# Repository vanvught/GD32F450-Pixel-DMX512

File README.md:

#GD32F450 Pixel DMX512

Features: 

- 16x 4 Universes pixel output
- 2x  1 Universe DMX output
- EEPROM for storing the configuration
- 1x I2C (display)
- 1x SPI
- 2x UART (WiFi , Bluetooth)

Firmware: [https://github.com/vanvught/GD32F450VI-DMX512-PIXEL](https://github.com/vanvught/GD32F450VI-DMX512-PIXEL)

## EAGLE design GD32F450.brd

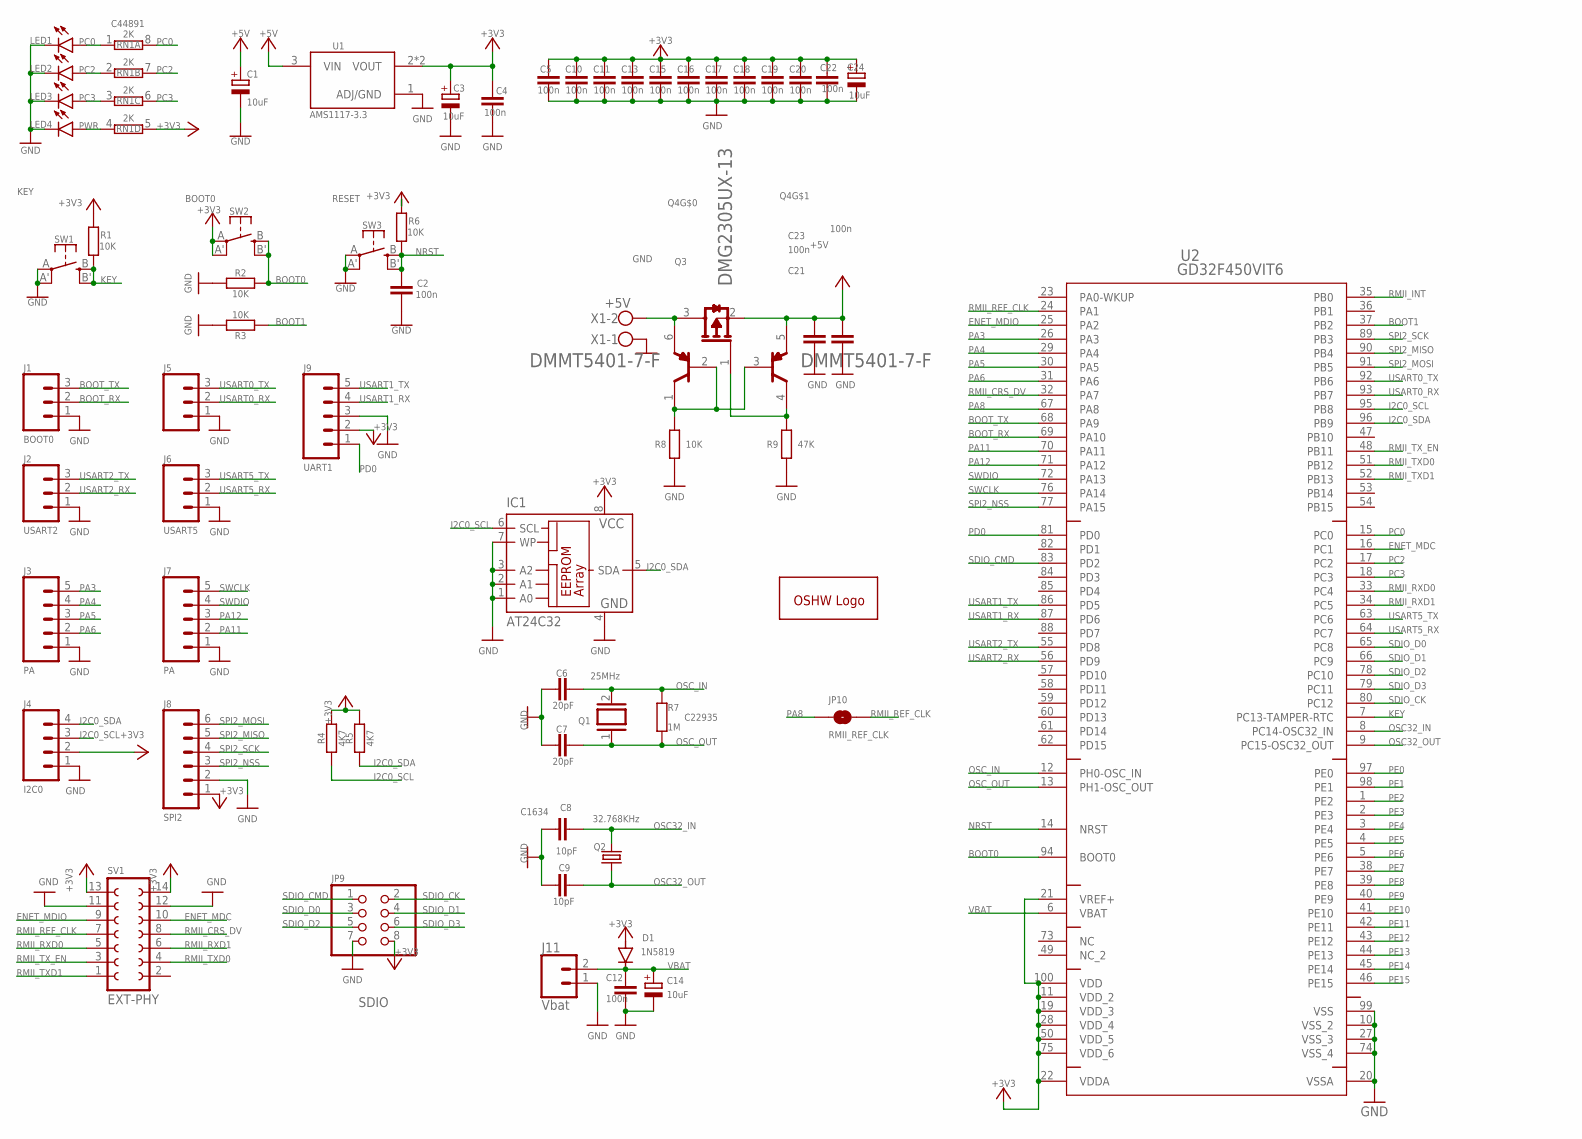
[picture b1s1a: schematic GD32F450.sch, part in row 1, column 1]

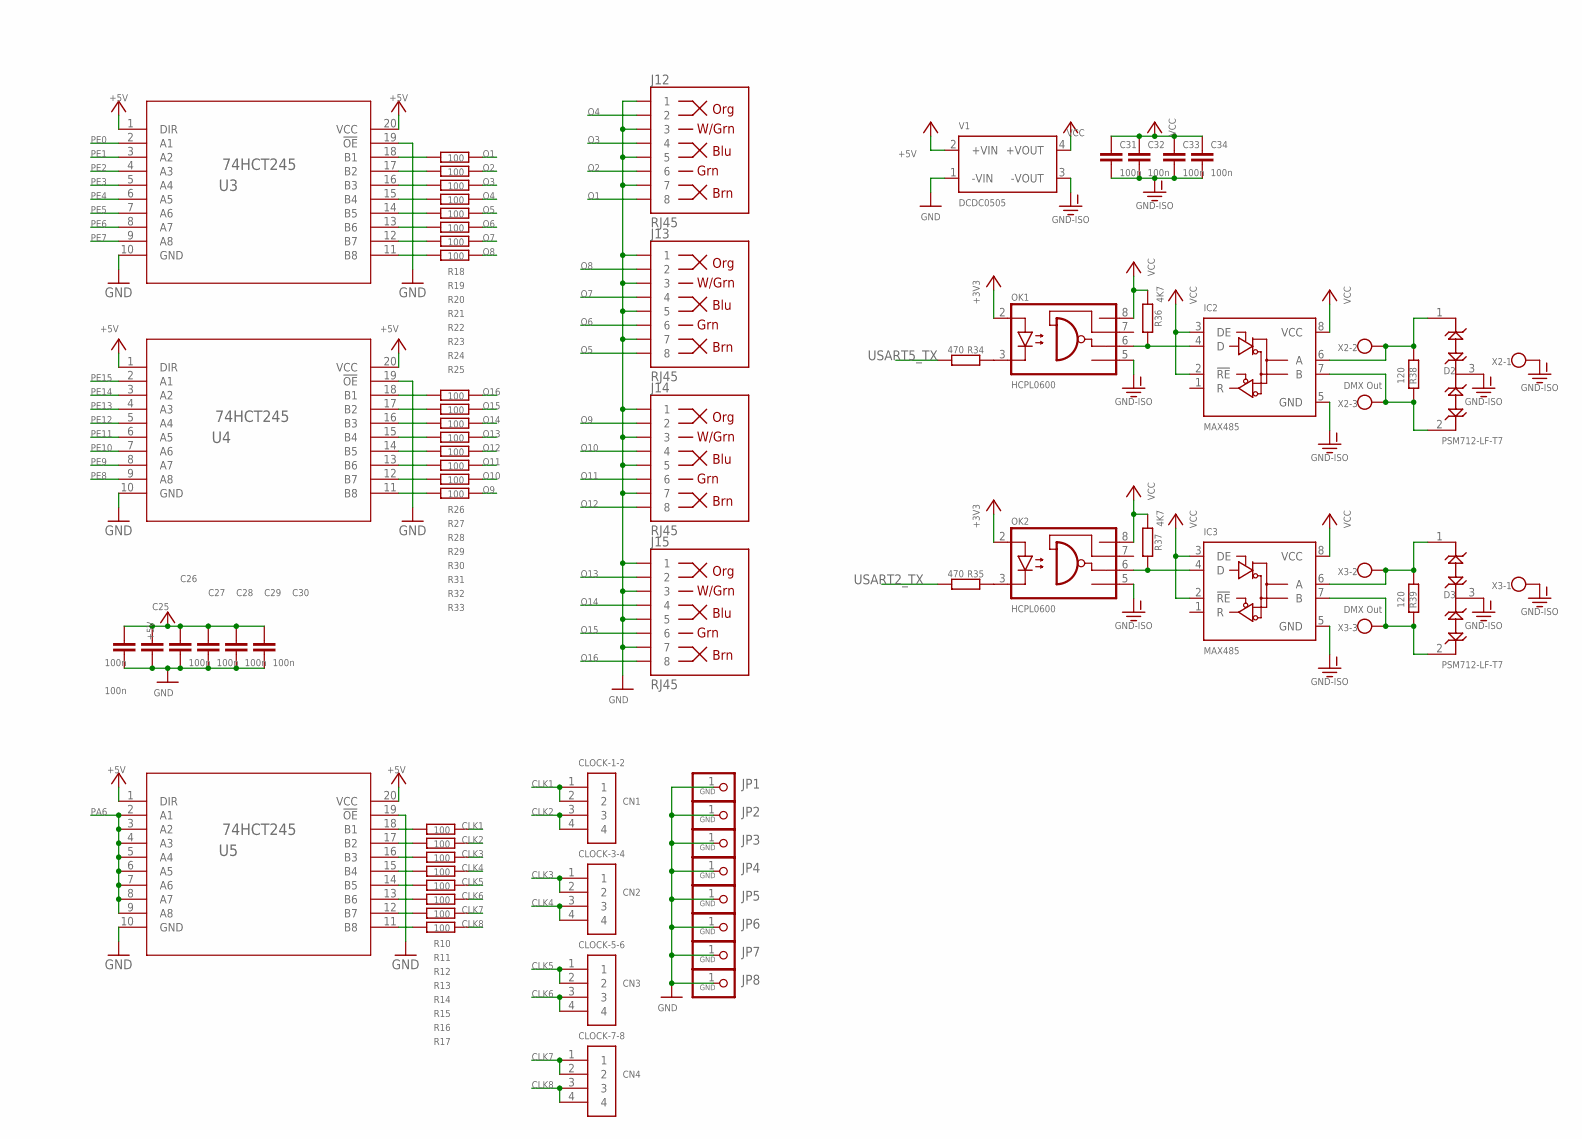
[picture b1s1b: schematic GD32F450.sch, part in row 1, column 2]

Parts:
C1, C3, C14, C24: 10uF; A/3216-18R; JLCPCB C7171
C2, C4, C5, C10, C11, C12, C13, C15, C16, C17, C18, C19, C20, C22, C25, C26, C27, C28, C29, C30, C31, C32, C33, C34: 100n; C0603; JLCPCB C14663
C6, C7: 20pF; C0603; JLCPCB C1648
C8, C9: 10pF; C0603; JLCPCB C1634
C21, C23: 100n; C0603
CN1: CLOCK-1-2; 1X04-CLEANBIG
CN2: CLOCK-3-4; 1X04-CLEANBIG
CN3: CLOCK-5-6; 1X04-CLEANBIG
CN4: CLOCK-7-8; 1X04-CLEANBIG
D1: 1N5819; SOD323-R; JLCPCB C191023
D2, D3: PSM712-LF-T7; SOT23-3; JLCPCB C32677
GOLD_ORB_SM1: OSHWLOGOLOGO5MM; OSHW_5MM
IC1: AT24C32; SO-08M
IC2, IC3: MAX485; D_R-PDSO-G8; JLCPCB C23492
J1: BOOT0; 1X03
J2: USART2; 1X03
J3, J7: PA; 1X05
J4: I2C0; 1X04
J5: USART0; 1X03
J6: USART5; 1X03
J8: SPI2; 1X06
J9: UART1; 1X05
J11: Vbat; 1X02_NO_SILK
J12, J13, J14, J15: RJ45; RJ45-8
JP1, JP2, JP3, JP4, JP5, JP6, JP7, JP8: GND; 1X01-CLEANBIG
JP9: SDIO; 2X04
JP10: RMII_REF_CLK; SMT-JUMPER_2_NO_NO-SILK
LED1: PC0; CHIP-LED0603
LED2: PC2; CHIP-LED0603
LED3: PC3; CHIP-LED0603
LED4: PWR; CHIP-LED0603
OK1, OK2: HCPL0600; SOIC08; JLCPCB C393524
Q1: 25MHz; QS
Q2: 32.768KHz; TC26H
Q3: DMG2305UX; DIODES_INC._DMG2305UX-13_0
Q4: DMMT5401; DIODES_DMMT5401-7-F_0
R1, R2, R3, R6: 10K; R0603; JLCPCB C25804
R4, R5: 4K7; R0402; JLCPCB C23162
R7: 1M; R0603; JLCPCB C22935
R8: 10K; R0402
R9: 47K; R0402
R10, R11, R12, R13, R14, R15, R16, R17, R18, R19, R20, R21, R22, R23, R24, R25, R26, R27, R28, R29, R30, R31, R32, R33: 100; R0402
R34, R35: 470; R0402; JLCPCB C25117
R36, R37: 4K7; R0402; JLCPCB C275348
R38, R39: 120; R0402; JLCPCB C25079
RN1: 2K; 4X0402ARV341; JLCPCB C44891
SV1: EXT-PHY; FE07-2W
SW1: KEY; EVQ-Q2
SW2: BOOT0; EVQ-Q2; JLCPCB C221880
SW3: RESET; EVQ-Q2
U1: AMS1117-3.3; SOT229P700X180-4N
U2: GD32F450VIT6; LQFP100
U3, U4, U5: 74HCT245; PW20
V1: DCDC0505; TME
X1: +5V; W237-102
X2, X3: DMX Out; W237-103

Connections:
+3V3: C3.+, C4.1, C5.1, C10.1, C11.1, C13.1, C15.1, C16.1, C17.1, C18.1, C19.1, C20.1, C22.1, C24.+, D1.A, IC1.8 (VCC), J4.2, J8.1, J9.2, JP9.8, OK1.2 (A), OK2.2 (A), R1.2, R4.2, R5.2, R6.2, RN1.5 (2), SV1.13, SV1.14, SW2.A, SW2.A' (P1), U1.2 (VOUT), U1.4 (VOUT), U2.11 (VDD_2), U2.19 (VDD_3), U2.21 (VREF+), U2.22 (VDDA), U2.28 (VDD_4), U2.50 (VDD_5), U2.75 (VDD_6), U2.100 (VDD)
+5V: C1.+, C21.1, C23.1, C25.1, C26.1, C27.1, C28.1, C29.1, C30.1, Q3.2 (S), Q4.5 (E2), U1.3 (VIN), U3.1 (DIR), U3.20 (VCC), U4.1 (DIR), U4.20 (VCC), U5.1 (DIR), U5.20 (VCC), V1.2 (+VIN)
BOOT0: R2.2, SW2.B (S), SW2.B' (S1), U2.94 (BOOT0)
BOOT1: R3.1, U2.37 (PB2)
BOOT_RX: J1.2, U2.69 (PA10)
BOOT_TX: J1.3, U2.68 (PA9)
CLK1: CN1.1, CN1.2, R10.2
CLK2: CN1.3, CN1.4, R11.2
CLK3: CN2.1, CN2.2, R12.2
CLK4: CN2.3, CN2.4, R13.2
CLK5: CN3.1, CN3.2, R14.2
CLK6: CN3.3, CN3.4, R15.2
CLK7: CN4.1, CN4.2, R16.2
CLK8: CN4.3, CN4.4, R17.2
ENET_MDC: SV1.10, U2.16 (PC1)
ENET_MDIO: SV1.9, U2.25 (PA2)
GND: C1.-, C2.2, C3.-, C4.2, C5.2, C6.1, C7.1, C8.1, C9.1, C10.2, C11.2, C12.2, C13.2, C14.-, C15.2, C16.2, C17.2, C18.2, C19.2, C20.2, C21.2, C22.2, C23.2, C24.-, C25.2, C26.2, C27.2, C28.2, C29.2, C30.2, IC1.1 (A0), IC1.2 (A1), IC1.3 (A2), IC1.4 (GND), IC1.7 (WP), J1.1, J2.1, J3.1, J4.1, J5.1, J6.1, J7.1, J8.2, J9.3, J11.1, J12.1, J12.3, J12.5, J12.7, J13.1, J13.3, J13.5, J13.7, J14.1, J14.3, J14.5, J14.7, J15.1, J15.3, J15.5, J15.7, JP1.1, JP2.1, JP3.1, JP4.1, JP5.1, JP6.1, JP7.1, JP8.1, JP9.7, LED1.C, LED2.C, LED3.C, LED4.C, R2.1, R3.2, R8.1, R9.1, SV1.11, SV1.12, SW1.A, SW1.A' (P1), SW3.A, SW3.A' (P1), U1.1 (ADJ/GND), U2.10 (VSS_2), U2.20 (VSSA), U2.27 (VSS_3), U2.74 (VSS_4), U2.99 (VSS), U3.10 (GND), U3.19 (!OE), U4.10 (GND), U4.19 (!OE), U5.10 (GND), U5.19 (!OE), V1.1 (-VIN), X1.1
GND-ISO: C31.2, C32.2, C33.2, C34.2, D2.3, D3.3, IC2.5 (GND), IC3.5 (GND), OK1.5 (GND), OK2.5 (GND), V1.3 (-VOUT), X2.1, X3.1
I2C0_SCL: IC1.6 (SCL), J4.3, R4.1, U2.95 (PB8)
I2C0_SDA: IC1.5 (SDA), J4.4, R5.1, U2.96 (PB9)
KEY: R1.1, SW1.B (S), SW1.B' (S1), U2.7 (PC13-TAMPER-RTC)
unnamed: R18.1, U3.18 (B1)
unnamed: Q4.1 (C1), Q4.2 (B1), Q4.3 (B2), R8.2
unnamed: R19.1, U3.17 (B2)
unnamed: R20.1, U3.16 (B3)
unnamed: R21.1, U3.15 (B4)
unnamed: R22.1, U3.14 (B5)
unnamed: R23.1, U3.13 (B6)
unnamed: R24.1, U3.12 (B7)
unnamed: R25.1, U3.11 (B8)
unnamed: LED1.A, RN1.1
unnamed: LED2.A, RN1.2 (1)
unnamed: R26.1, U4.18 (B1)
unnamed: R27.1, U4.17 (B2)
unnamed: R28.1, U4.16 (B3)
unnamed: R29.1, U4.15 (B4)
unnamed: R30.1, U4.14 (B5)
unnamed: R31.1, U4.13 (B6)
unnamed: R32.1, U4.12 (B7)
unnamed: R33.1, U4.11 (B8)
unnamed: IC2.4 (D), OK1.6 (VO), R36.2
unnamed: OK1.3 (C), R34.2
unnamed: IC3.4 (D), OK2.6 (VO), R37.2
unnamed: OK2.3 (C), R35.2
unnamed: D2.1, IC2.6 (A), R38.1, X2.2
unnamed: LED3.A, RN1.3 (1)
unnamed: LED4.A, RN1.4 (1)
unnamed: D2.2, IC2.7 (B), R38.2, X2.3
unnamed: D3.2, IC3.7 (B), R39.2, X3.3
unnamed: D3.1, IC3.6 (A), R39.1, X3.2
unnamed: Q3.1 (G), Q4.4 (C2), R9.2
unnamed: Q3.3 (D), Q4.6 (E1), X1.2
unnamed: R10.1, U5.18 (B1)
unnamed: R11.1, U5.17 (B2)
unnamed: R12.1, U5.16 (B3)
unnamed: R13.1, U5.15 (B4)
unnamed: R14.1, U5.14 (B5)
unnamed: R15.1, U5.13 (B6)
unnamed: R16.1, U5.12 (B7)
unnamed: R17.1, U5.11 (B8)
NRST: C2.1, R6.1, SW3.B (S), SW3.B' (S1), U2.14 (NRST)
O1: J12.8, R18.2
O2: J12.6, R19.2
O3: J12.4, R20.2
O4: J12.2, R21.2
O5: J13.8, R22.2
O6: J13.6, R23.2
O7: J13.4, R24.2
O8: J13.2, R25.2
O9: J14.2, R33.2
O10: J14.4, R32.2
O11: J14.6, R31.2
O12: J14.8, R30.2
O13: J15.2, R29.2
O14: J15.4, R28.2
O15: J15.6, R27.2
O16: J15.8, R26.2
OSC32_IN: C8.2, Q2.2, U2.8 (PC14-OSC32_IN)
OSC32_OUT: C9.2, Q2.1, U2.9 (PC15-OSC32_OUT)
OSC_IN: C6.2, Q1.2, R7.2, U2.12 (PH0-OSC_IN)
OSC_OUT: C7.2, Q1.1, R7.1, U2.13 (PH1-OSC_OUT)
PA3: J3.5, U2.26 (PA3)
PA4: J3.4, U2.29 (PA4)
PA5: J3.3, U2.30 (PA5)
PA6: J3.2, U2.31 (PA6), U5.2 (A1), U5.3 (A2), U5.4 (A3), U5.5 (A4), U5.6 (A5), U5.7 (A6), U5.8 (A7), U5.9 (A8)
PA8: JP10.1, U2.67 (PA8)
PA11: J7.2, U2.70 (PA11)
PA12: J7.3, U2.71 (PA12)
PC0: RN1.8 (2), U2.15 (PC0)
PC2: RN1.7 (2), U2.17 (PC2)
PC3: RN1.6 (2), U2.18 (PC3)
PD0: J9.1, U2.81 (PD0)
PE0: U2.97 (PE0), U3.2 (A1)
PE1: U2.98 (PE1), U3.3 (A2)
PE2: U2.1 (PE2), U3.4 (A3)
PE3: U2.2 (PE3), U3.5 (A4)
PE4: U2.3 (PE4), U3.6 (A5)
PE5: U2.4 (PE5), U3.7 (A6)
PE6: U2.5 (PE6), U3.8 (A7)
PE7: U2.38 (PE7), U3.9 (A8)
PE8: U2.39 (PE8), U4.9 (A8)
PE9: U2.40 (PE9), U4.8 (A7)
PE10: U2.41 (PE10), U4.7 (A6)
PE11: U2.42 (PE11), U4.6 (A5)
PE12: U2.43 (PE12), U4.5 (A4)
PE13: U2.44 (PE13), U4.4 (A3)
PE14: U2.45 (PE14), U4.3 (A2)
PE15: U2.46 (PE15), U4.2 (A1)
RMII_CRS_DV: SV1.8, U2.32 (PA7)
RMII_INT: U2.35 (PB0)
RMII_REF_CLK: JP10.2, SV1.7, U2.24 (PA1)
RMII_RXD0: SV1.5, U2.33 (PC4)
RMII_RXD1: SV1.6, U2.34 (PC5)
RMII_TXD0: SV1.4, U2.51 (PB12)
RMII_TXD1: SV1.1, U2.52 (PB13)
RMII_TX_EN: SV1.3, U2.48 (PB11)
SDIO_CK: JP9.2, U2.80 (PC12)
SDIO_CMD: JP9.1, U2.83 (PD2)
SDIO_D0: JP9.3, U2.65 (PC8)
SDIO_D1: JP9.4, U2.66 (PC9)
SDIO_D2: JP9.5, U2.78 (PC10)
SDIO_D3: JP9.6, U2.79 (PC11)
SPI2_MISO: J8.5, U2.90 (PB4)
SPI2_MOSI: J8.6, U2.91 (PB5)
SPI2_NSS: J8.3, U2.77 (PA15)
SPI2_SCK: J8.4, U2.89 (PB3)
SWCLK: J7.5, U2.76 (PA14)
SWDIO: J7.4, U2.72 (PA13)
USART0_RX: J5.2, U2.93 (PB7)
USART0_TX: J5.3, U2.92 (PB6)
USART1_RX: J9.4, U2.87 (PD6)
USART1_TX: J9.5, U2.86 (PD5)
USART2_RX: J2.2, U2.56 (PD9)
USART2_TX: J2.3, R35.1, U2.55 (PD8)
USART5_RX: J6.2, U2.64 (PC7)
USART5_TX: J6.3, R34.1, U2.63 (PC6)
VBAT: C12.1, C14.+, D1.C, J11.2, U2.6 (VBAT)
VCC: C31.1, C32.1, C33.1, C34.1, IC2.2 (!RE), IC2.3 (DE), IC2.8 (VCC), IC3.2 (!RE), IC3.3 (DE), IC3.8 (VCC), OK1.8 (VCC), OK2.8 (VCC), R36.1, R37.1, V1.4 (+VOUT)

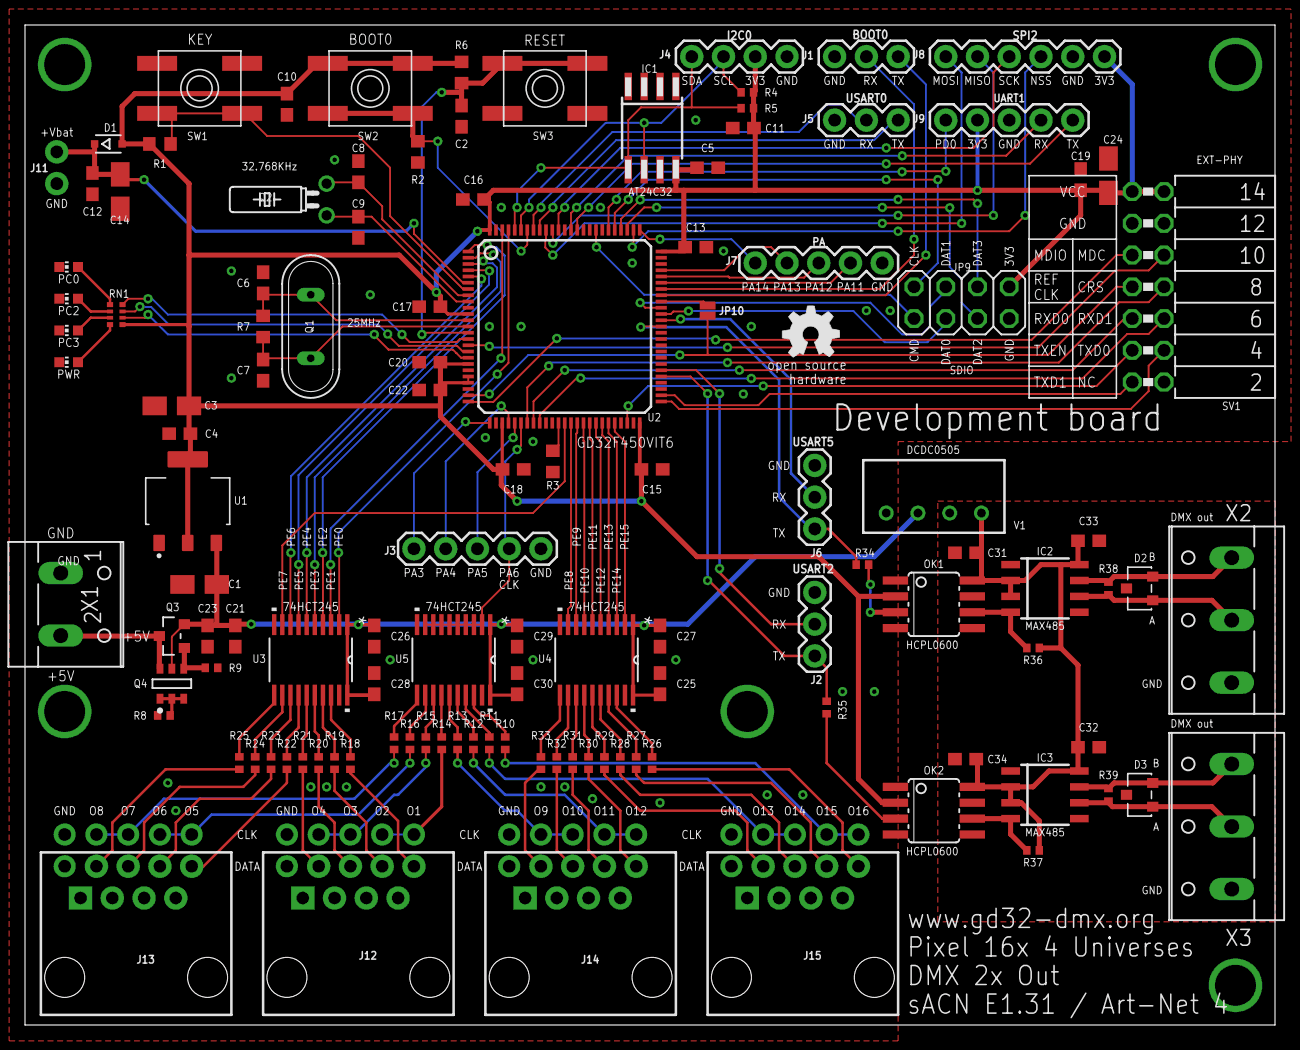
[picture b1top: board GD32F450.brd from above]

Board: 2 copper layers, 100.0 x 80.0 mm, 132 parts (0 on the bottom side), 137 nets.

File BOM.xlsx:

Qty | Designator | Footprint | Comment | LCSC Part #
4 | C1, C3, C14, C24 | A/3216-18R | 10uF | C7171
26 | C2, C4, C5, C10, C11, C12, C13, C15, C16, C17, C18, C19, C20, C22,C21, C23 , C2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 | C0603 | 100n | C14663
2 | C6, C7 | C0603 | 20pF | C1648
2 | C8, C9 | C0603 | 10pF | C1634
1 | D1 | SOD323-R | 1N5819 | C191023
2 | D2, D3 | SOT23-3 | PSM712-LF-T7 | C32677
1 | IC1 | SO-08M | AT24C32 | C2688466
2 | IC2, IC3 | D_R-PDSO-G8 | MAX485 | C23492
4 | LED1, LED2 , LED3, LED4 | CHIP-LED0603 | CHIP-LED0603 | C72043
2 | OK1, OK2 | SOIC08 | HCPL0600 | C393524
1 | Q3 | DIODES_INC._DMG2305UX-13_0 | DMG2305UX | C150470
1 | Q4 | DIODES_DMMT5401-7-F_0 | DMMT5401-7-F_0_0 | C154733
4 | R1, R2, R3, R6 | R0603 | 10K | C25804
24 | R10, R11, R12, R13, R14, R15, R16, R17, R18, R19, R20, R21, R22, R23, R24, R25,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 | R0402 | 100 | C25076
2 | R38, R39 | R0402 | 120 | C25079
2 | R34, R35 | R0402 | 470 | C25117
4 | R4, R5, R36, R37 | R0402 | 4K7 | C25900
1 | R7 | R0603 | 1M | C22935
1 | R8 | R0402 | 10K | C25117
1 | R9 | R0402 | 47K | C25792
1 | RN1 | 4X0402ARV341 | 2K | C44891
3 | SW1, SW2, SW3 | EVQ-Q2 | SPST 6*6mm Tactile Switch | C221880
1 | U1 | SOT23-5 | AMS1117-3.3 | C6186
1 | U2 | LQFP100 | GD32F450VIT6 | C98441
2 | U3, U4, U5 | PW20 | 74HCT245 | C10910
95

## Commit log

2022-12-10 Fixed R8 in BOM
2024-09-23 Added FUNDING.yml

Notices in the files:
parts and their libraries:
SparkFun-Connectors: Licensing: Creative Commons ShareAlike 4.0 International - https://creativecommons.org/licenses/by-sa/4.0
COPYRIGHT: Copyright (C) 2022 Ultra Librarian. All rights reserved.
